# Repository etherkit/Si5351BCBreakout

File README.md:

Si5351B/C Breakout Board
=====================

This repository hosts the KiCad project files for the Si5351B/C Breakout 
Board, as well as the schematic in PDF format.

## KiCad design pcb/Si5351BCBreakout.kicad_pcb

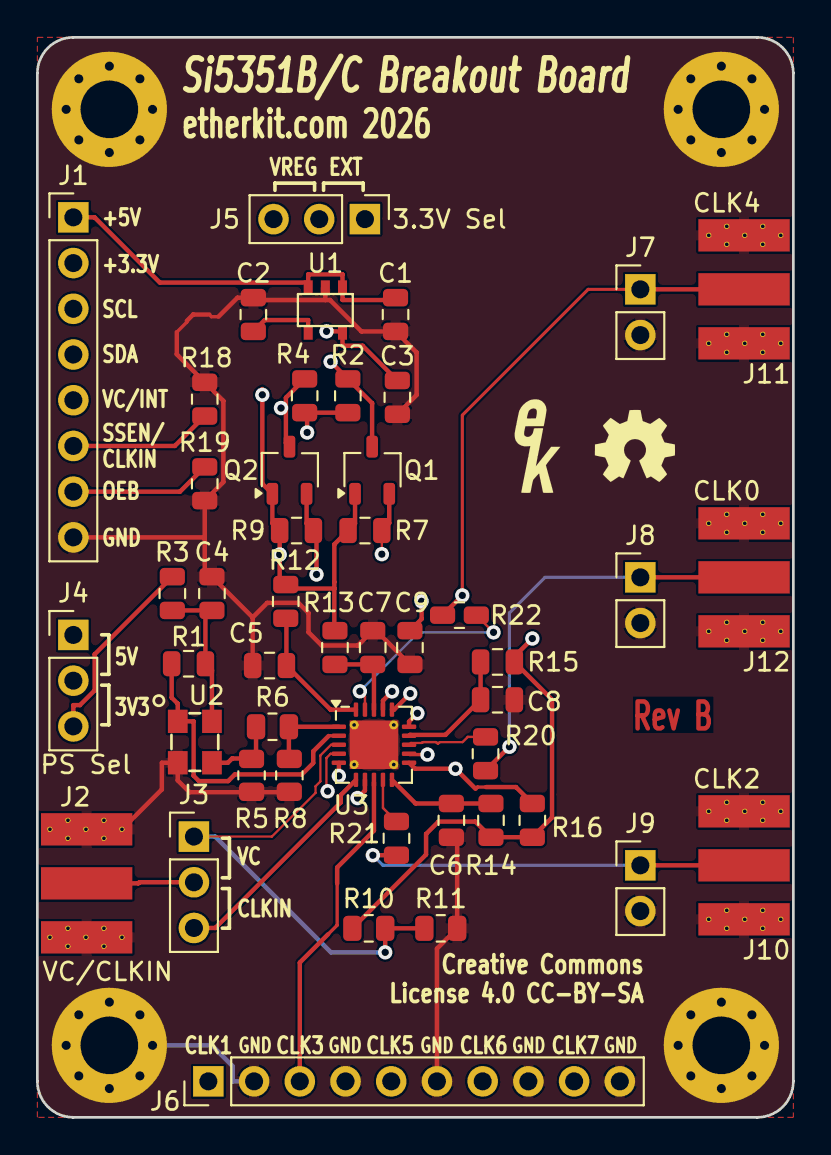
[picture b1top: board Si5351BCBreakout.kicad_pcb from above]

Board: 4 copper layers, 42.0 x 60.0 mm, 52 parts (0 on the bottom side), 35 nets.

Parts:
C1, C3: 4.7u; C_0805_2012Metric
C2: 10n; C_0805_2012Metric
C4, C5, C6, C7, C8, C9: 100n; C_0805_2012Metric
H1, H2, H3, H4: MountingHole_Pad; MountingHole_3.2mm_M3_Pad_Via
J1: Power/IO; PinHeader_1x08_P2.54mm_Vertical
J2: VC/CLKIN; SMA-ENDLAUNCH
J3: VC/CLKIN; PinHeader_1x03_P2.54mm_Vertical
J4: PS Sel; PinHeader_1x03_P2.54mm_Vertical
J5: 3.3V Sel; PinHeader_1x03_P2.54mm_Vertical
J6: CLK3-CLK7; PinHeader_1x10_P2.54mm_Vertical
J7: CLK4; PinHeader_1x02_P2.54mm_Vertical
J8: CLK0; PinHeader_1x02_P2.54mm_Vertical
J9: CLK2; PinHeader_1x02_P2.54mm_Vertical
J10: CLK2; SMA-ENDLAUNCH
J11: CLK4; SMA-ENDLAUNCH
J12: CLK0; SMA-ENDLAUNCH
Q1, Q2: BSS138; TSOT-23
R1, R20, R21, R22: 0; R_0805_2012Metric
R2, R4, R7, R9, R10, R11, R18, R19: 10k; R_0805_2012Metric
R3, R12, R13, R14, R15, R16: 10; R_0805_2012Metric
R5, R8: 300; R_0805_2012Metric
R6: 18; R_0805_2012Metric
Ref**: Val**; EtherkitLogoSmall
U1: LP2985-3.3; SOT23-5
U2: ASTX-H11-25.000MHZ-T
U3: Si5351B/C; QFN-20-1EP_4x4mm_P0.5mm_EP2.7x2.7mm_ThermalVias

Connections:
+3.3V: J1.2, J5.3
+3.3VREG: J4.3, J5.2, Q1.1 (G), Q2.1 (G), R3.1, R7.1, R9.1, R10.1, R12.1, R13.1, R14.1, R15.1, R16.1
+5V: C1.1, J1.1, J4.1, U1.1 (VIN), U1.3 (ON)
/CLK0_OUT: J8.1, J12.1 (In), R20.1
/CLK2_OUT: J9.1, J10.1 (In), R21.1
/CLK4_OUT: J7.1, J11.1 (In), R22.1
CLK0: R20.2, U3.13 (CLK0)
CLK1: J6.1, U3.12 (CLK1)
CLK2: R21.2, U3.9 (CLK2)
CLK3: J6.3, U3.8 (CLK3)
CLK4: R22.2, U3.19 (CLK4)
CLK5: J6.5, U3.17 (CLK5)
CLK6: J6.7, U3.16 (CLK6)
CLK7: J6.9, U3.15 (CLK7)
GND: C1.2, C2.2, C3.2, C4.2, C5.2, C6.2, C7.2, C8.2, C9.2, H1.1 (1_1), H2.1 (1_1), H3.1 (1_1), H4.1 (1_1), J1.8, J2.2 (Ext), J6.2, J6.4, J6.6, J6.8, J6.10, J7.2, J8.2, J9.2, J10.2 (Ext), J11.2 (Ext), J12.2 (Ext), R5.2, R8.2, R11.2, R18.1, R19.1, U1.2 (GND), U2.2 (GND), U3.21 (GND)
unnamed: J1.3, Q1.3 (D), R2.2
unnamed: J1.4, Q2.3 (D), R4.2
unnamed: J2.1 (In), J3.2
unnamed: J4.2, R2.1, R4.1
unnamed: C3.1, J5.1, U1.5 (VOUT)
unnamed: Q1.2 (S), R7.2, U3.4 (SCL)
unnamed: Q2.2 (S), R9.2, U3.5 (SDA)
unnamed: C2.1, U1.4 (BP)
unnamed: R1.2, U2.1 (OE), U3.2 (XB)
unnamed: R5.1, R6.1, U2.3 (OUT)
unnamed: C4.1, R1.1, R3.2, U2.4 (VDD)
unnamed: C5.1, R12.2, U3.20 (VDD)
unnamed: C9.1, R16.2, U3.11 (VDDOA)
unnamed: C6.1, R14.2, U3.10 (VDDOB)
unnamed: C7.1, R13.2, U3.18 (VDDOC)
unnamed: C8.1, R15.2, U3.14 (VDDOD)
unnamed: R6.2, R8.1, U3.1 (XA)
OEB: J1.7, R19.2, U3.7 (OEB)
SSEN_CLKIN: J1.6, J3.3, R18.2, U3.6 (SSEN/CLKIN)
VC_INTR: J1.5, J3.1, R10.2, R11.1, U3.3 (VC/INTR)

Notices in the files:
pcb/Si5351BCBreakout.kicad_pcb:
Creative Commons
License 4.0 CC-BY-SA
